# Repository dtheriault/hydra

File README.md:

The Hydra Project
======================================================================================

The Hydra project is a collaborative effort between N1GP and NO1D in an attempt
to produce a 'n' port CW/RTTY Skimmer platform based on RTL SDR technology.

The work is heavily leveraged from existing projects such as cuSDR and rtl-sdr 
development efforts.  

Changes and focus has been optimizing and supporting small embedded platforms such
as the Odroid C1/U3/XU3, Nvidia TK1 and RaspberryPI which may or may not be viable
platforms to execute on. 

The git repo allows us to share code changes easily using GIT and utilize GitHub to 
track issues and changes.  In the end, Rick will push changes made here up stream
to main projects librtlhpsdr and cusdr should they be deemed suitible for mainstream
users.

Challenges:
======================================================================================

    -- Optimizing code bases to run fast/efficiently on ARM based platforms
    -- Providing reliable support for up to 8 RTL dongles
    -- Create tools useful for calibration of RTL dongles for accurate CW Skimmer spot
       reporting in the Reverse Beacon Network (RBN).
    -- Develop unique hardware which includes front end filters, attenuator, mixer, 
       multiport coupler, amplifiers to ease integration with low cost RTLSDR dongles.
    -- Unique hardware packaging 

Project Organization:
======================================================================================
    -- Hydra             Top Level

      -- Software         Software Top Level
          -- librtlsdr    RTL Libraries and tools
          -- cusdrk       cuSDR GUI Application
          -- plotter      Skimmer Plotter, QRZ/RBN tools

      -- Hardware         Hardware Top Level
          -- Schematic    Schematic data in Eagle format
          -- Boards       ditto
          -- BOM          BOM files
          -- Mechanicals  Hardware Case information

      -- Documentation
          -- Specifications	
          -- Test Plans		
          -- Measurement Data

      -- Testing
          -- Scripts and Test Plans

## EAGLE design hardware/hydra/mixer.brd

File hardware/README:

This is the HW tree, schematics, pcb layouts, BOM's etc.

-----------------------------------------------------------------------------
Change Log:

25.Jun.2015  Initial submit of hardware files for Eagle development

-----------------------------------------------------------------------------
Directories: 

medusa/hardware

        top level hardware tree

hydra/

        Eagle schematic and board files for Receiver and Mixer boards
        Includes first pass BOM
        Includes .pdf's of board layouts suitable for printing

libraries/

          Eagle custom parts library files.  Add to Eagle ${EAGLE_LIBRARIES} 
          directory.

multicoupler/

          Early 8 port 75 ohm multi-coupler using Minicircuits component

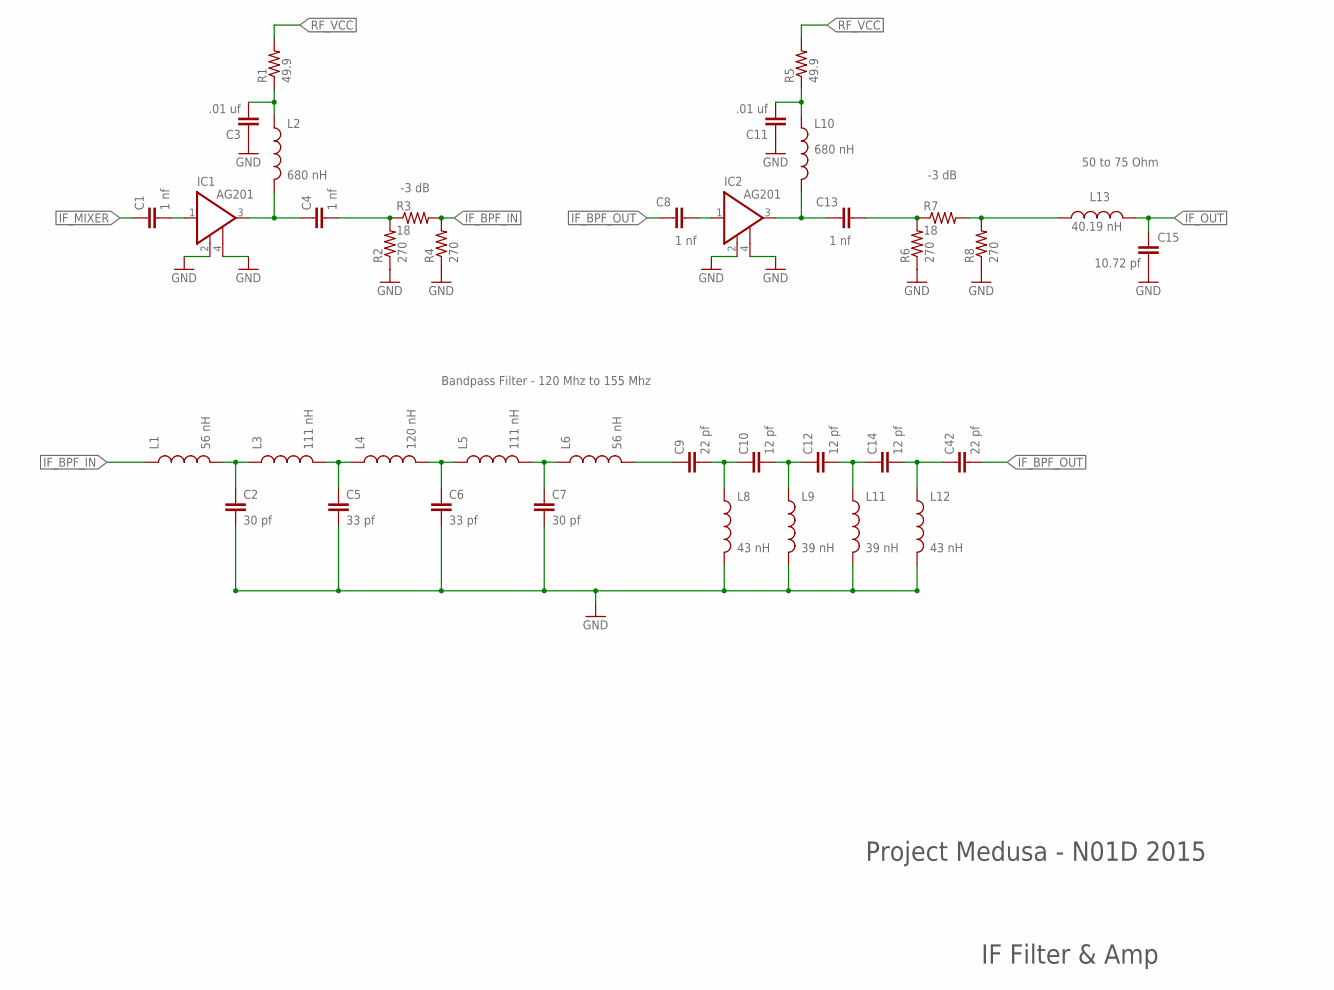
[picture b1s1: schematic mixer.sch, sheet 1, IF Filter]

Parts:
C1, C4, C8, C13: 1 nf; 0805
C2, C7: 30 pf; 0805
C3, C11: .01 uf; 0805
C5, C6: 33 pf; 0805
C9, C42: 22 pf; 0805
C10, C12, C14: 12 pf; 0805
C15: 10.72 pf; 0805
IC1, IC2: AG201; WW
L1, L6: 56 nH; 318-2
L2, L10: 680 nH; 0805
L3, L5: 111 nH; 319-2
L4: 120 nH; 318-2
L8, L12: 43 nH; 457-43
L9, L11: 39 nH; 457-39
L13: 40.19 nH; C0402
R1, R5: 49.9; 0805
R2, R4, R6, R8: 270; 1206
R3, R7: 18; 1206

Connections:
GND: C2.2, C3.1, C5.2, C6.2, C7.2, C11.1, C15.1, IC1.2 (GND), IC1.4 (GND), IC2.2 (GND), IC2.4 (GND), L8.P$2 (2), L9.P$2 (2), L11.P$2 (2), L12.P$2 (2), R2.1, R4.1, R6.1, R8.1; also elsewhere on the board
IF_BPF_IN: L1.P$1 (1), R3.2, R4.2
IF_BPF_OUT: C8.1, C42.2
IF_MIXER: C1.1; also elsewhere on the board
IF_OUT: C15.2, L13.2; also elsewhere on the board
unnamed: C2.1, L1.P$2 (2), L3.P$1 (1)
unnamed: C5.1, L3.P$2 (2), L4.P$1 (1)
unnamed: C6.1, L4.P$2 (2), L5.P$1 (1)
unnamed: C7.1, L5.P$2 (2), L6.P$1 (1)
unnamed: C9.1, L6.P$2 (2)
unnamed: C9.2, C10.1, L8.P$1 (1)
unnamed: C10.2, C12.1, L9.P$1 (1)
unnamed: C12.2, C14.1, L11.P$1 (1)
unnamed: C1.2, IC1.1 (RFIN)
unnamed: C4.1, IC1.3 (RFOUT/DCIN), L2.2
unnamed: C3.2, L2.1, R1.1
unnamed: C4.2, R2.2, R3.1
unnamed: C8.2, IC2.1 (RFIN)
unnamed: C13.1, IC2.3 (RFOUT/DCIN), L10.2
unnamed: C11.2, L10.1, R5.1
unnamed: C13.2, R6.2, R7.1
unnamed: L13.1, R7.2, R8.2
unnamed: C14.2, C42.1, L12.P$1 (1)
RF_VCC: R1.2, R5.2; also elsewhere on the board

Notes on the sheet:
Bandpass Filter - 120 Mhz to 155 Mhz
50 to 75 Ohm
-3 dB
Project Medusa - N01D 2015
IF Filter & Amp

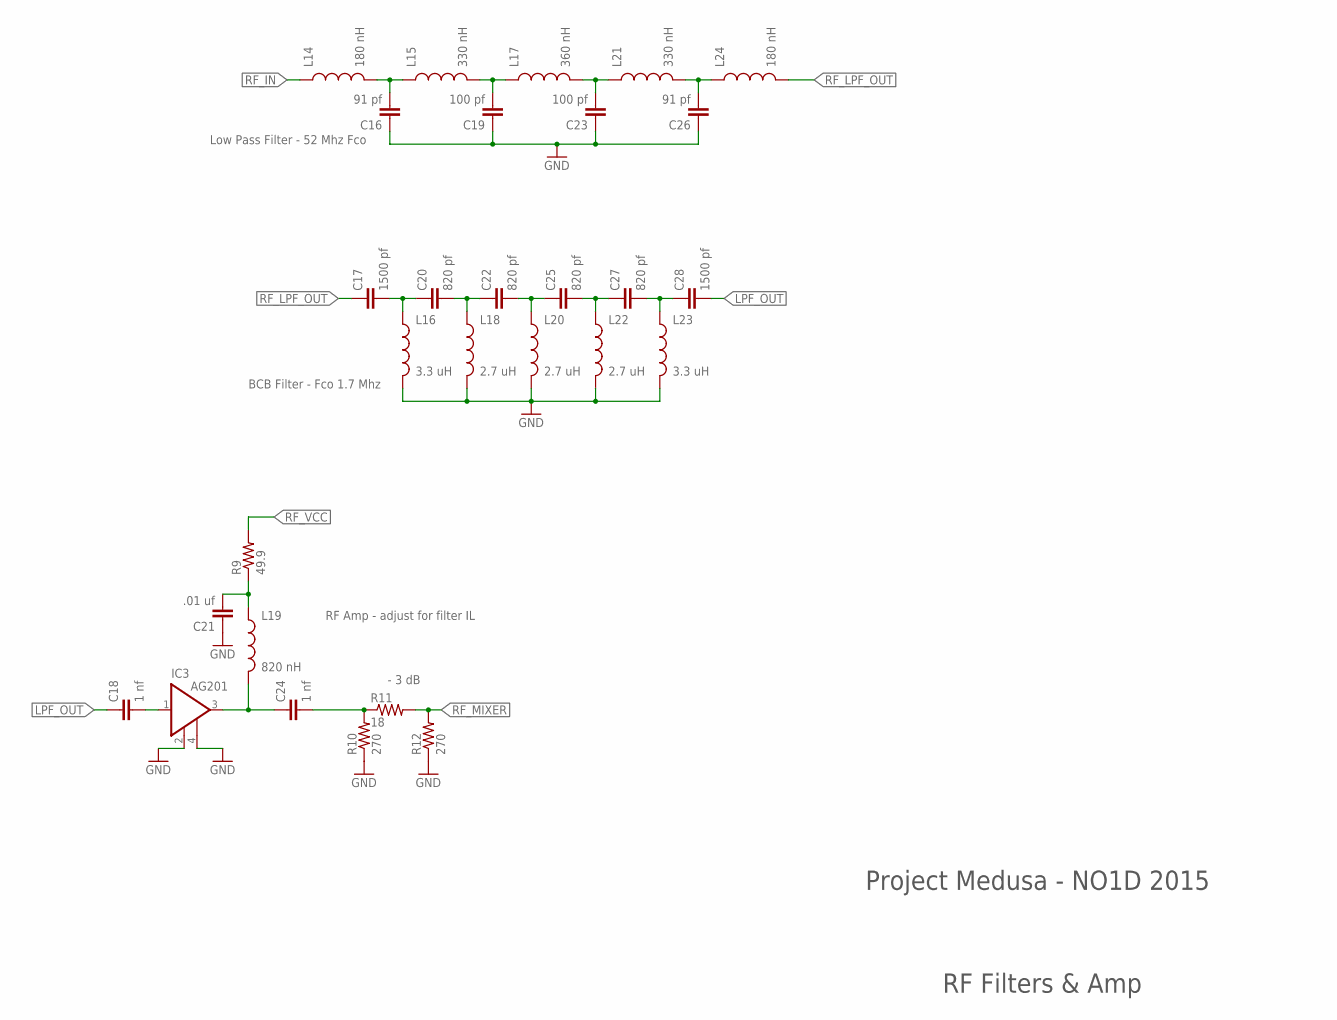
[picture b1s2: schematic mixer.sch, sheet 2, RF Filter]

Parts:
C16, C26: 91 pf; 0805
C17, C28: 1500 pf; 0805
C18, C24: 1 nf; 0805
C19, C23: 100 pf; 0805
C20, C22, C25, C27: 820 pf; 0805
C21: .01 uf; 0805
IC3: AG201; WW
L14, L24: 180 nH; 438-2-180
L15, L21: 330 nH; 438-2-330
L16, L23: 3.3 uH; RLB0912
L17: 360 nH; 438-2-360
L18, L20, L22: 2.7 uH; RLB0912
L19: 820 nH; 0805
R9: 49.9; 0805
R10, R12: 270; 1206
R11: 18; 1206

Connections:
GND: C16.1, C19.1, C21.1, C23.1, C26.1, IC3.2 (GND), IC3.4 (GND), L16.2, L18.2, L20.2, L22.2, L23.2, R10.1, R12.1; also elsewhere on the board
LPF_OUT: C18.1, C28.2
unnamed: C18.2, IC3.1 (RFIN)
unnamed: C24.1, IC3.3 (RFOUT/DCIN), L19.2
unnamed: C21.2, L19.1, R9.1
unnamed: C24.2, R10.2, R11.1
unnamed: C16.2, L14.P$2 (2), L15.P$1 (1)
unnamed: C19.2, L15.P$2 (2), L17.P$1 (1)
unnamed: C23.2, L17.P$2 (2), L21.P$1 (1)
unnamed: C26.2, L21.P$2 (2), L24.P$1 (1)
unnamed: C17.2, C20.1, L16.1
unnamed: C20.2, C22.1, L18.1
unnamed: C22.2, C25.1, L20.1
unnamed: C25.2, C27.1, L22.1
unnamed: C27.2, C28.1, L23.1
RF_IN: L14.P$1 (1); also elsewhere on the board
RF_LPF_OUT: C17.1, L24.P$2 (2)
RF_MIXER: R11.2, R12.2; also elsewhere on the board
RF_VCC: R9.2; also elsewhere on the board

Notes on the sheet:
Low Pass Filter - 52 Mhz Fco
BCB Filter - Fco 1.7 Mhz
- 3 dB
RF Amp - adjust for filter IL
Project Medusa - NO1D 2015
RF Filters & Amp

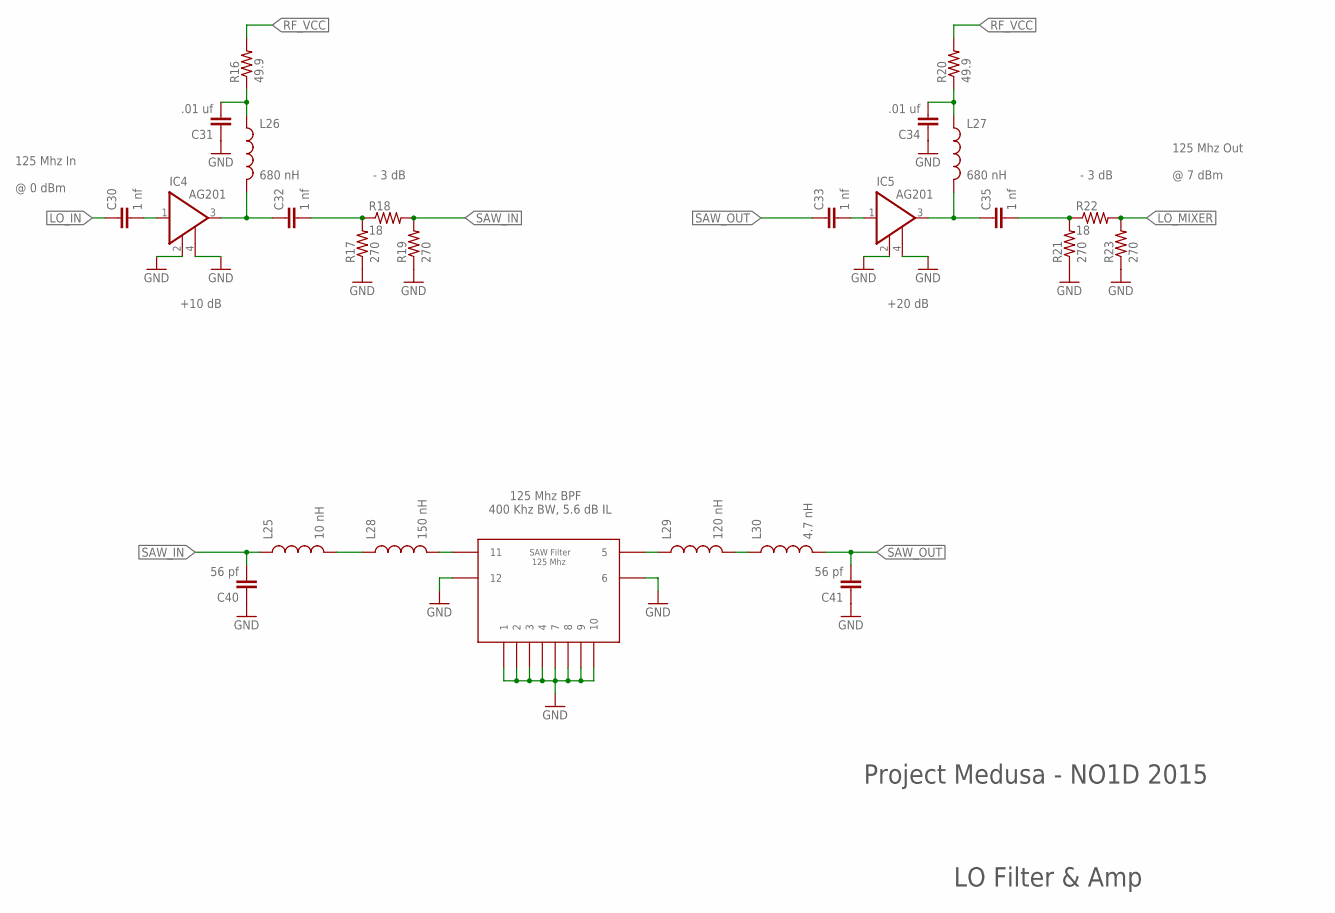
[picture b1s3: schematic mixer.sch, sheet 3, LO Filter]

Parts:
C30, C32, C33, C35: 1 nf; 0805
C31, C34: .01 uf; 0805
C40, C41: 56 pf; 0805
IC4, IC5: AG201; WW
L25: 10 nH; C0402
L26, L27: 680 nH; 0805
L28: 150 nH; 0805
L29: 120 nH; 0805
L30: 4.7 nH; C0402
R16, R20: 49.9; 0805
R17, R19, R21, R23: 270; 1206
R18, R22: 18; 1206
SAW1: SAW-125MHZ; SAW-125M-SMP

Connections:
GND: C31.1, C34.1, C40.1, C41.1, IC4.2 (GND), IC4.4 (GND), IC5.2 (GND), IC5.4 (GND), R17.1, R19.1, R21.1, R23.1, SAW1.P$1 (1), SAW1.P$2 (2), SAW1.P$3 (3), SAW1.P$4 (4), SAW1.P$6 (6), SAW1.P$7 (7), SAW1.P$8 (8), SAW1.P$9 (9), SAW1.P$10 (10), SAW1.P$12 (12); also elsewhere on the board
LO_IN: C30.1; also elsewhere on the board
LO_MIXER: R22.2, R23.2; also elsewhere on the board
unnamed: C30.2, IC4.1 (RFIN)
unnamed: C32.1, IC4.3 (RFOUT/DCIN), L26.2
unnamed: C31.2, L26.1, R16.1
unnamed: C32.2, R17.2, R18.1
unnamed: C33.2, IC5.1 (RFIN)
unnamed: C35.1, IC5.3 (RFOUT/DCIN), L27.2
unnamed: C34.2, L27.1, R20.1
unnamed: C35.2, R21.2, R22.1
unnamed: L25.2, L28.1
unnamed: L29.2, L30.1
unnamed: L28.2, SAW1.P$11 (11)
unnamed: L29.1, SAW1.P$5 (5)
RF_VCC: R16.2, R20.2; also elsewhere on the board
SAW_IN: C40.2, L25.1, R18.2, R19.2
SAW_OUT: C33.1, C41.2, L30.2

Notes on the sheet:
125 Mhz In @ 0 dBm
125 Mhz Out @ 7 dBm
+10 dB
+20 dB
- 3 dB
125 Mhz BPF 400 Khz BW, 5.6 dB IL
Project Medusa - NO1D 2015
LO Filter & Amp

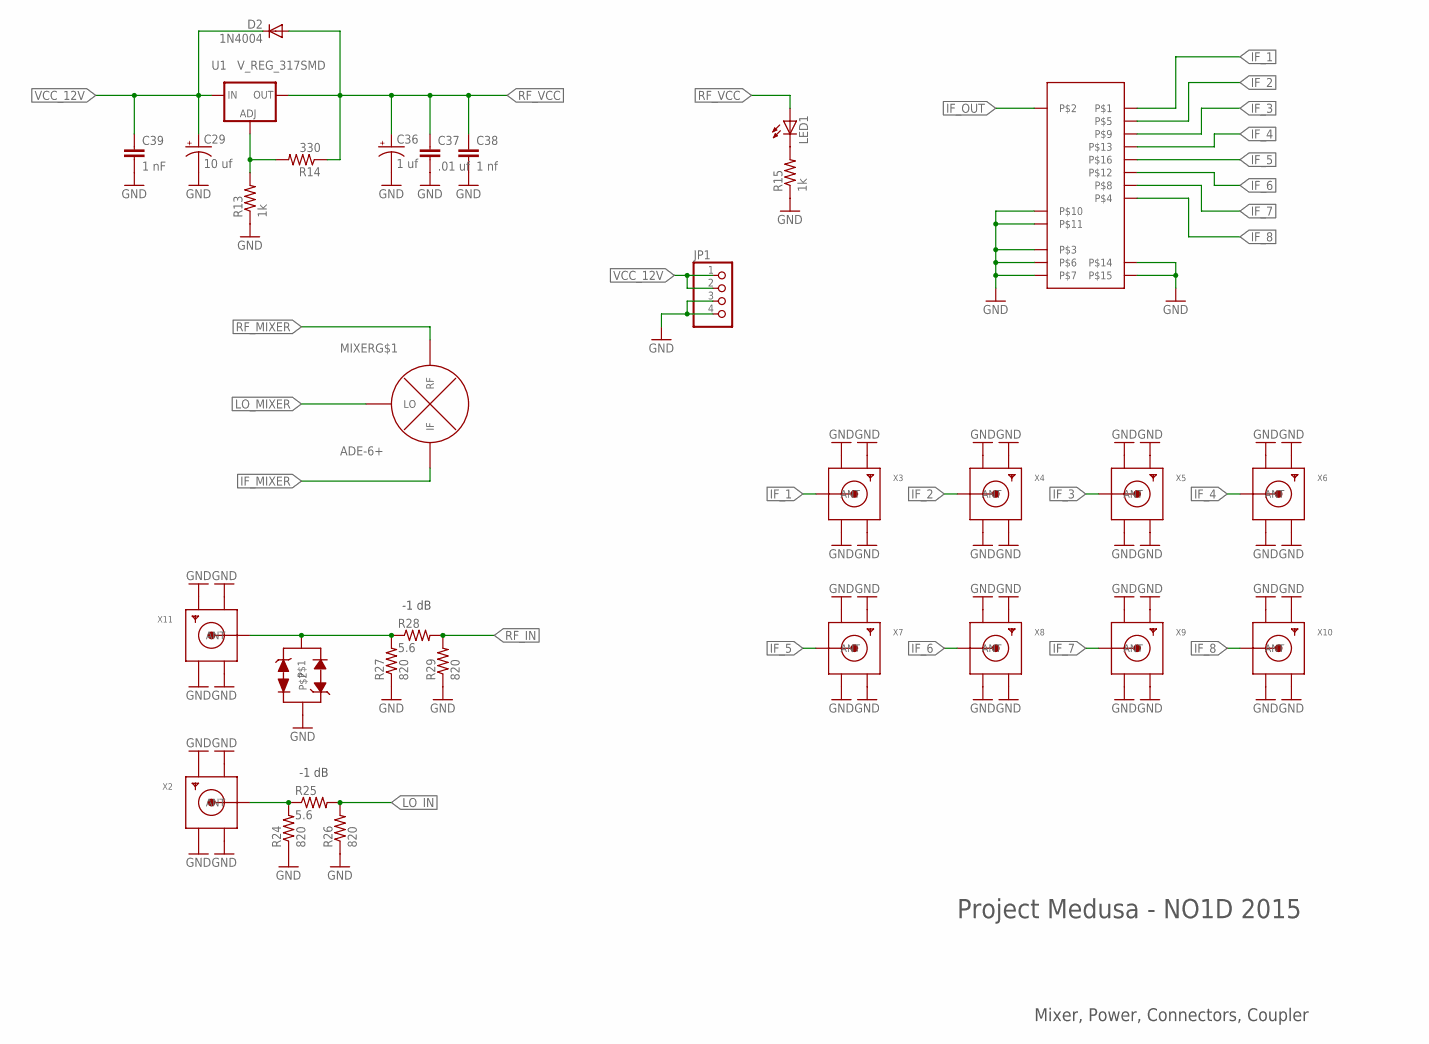
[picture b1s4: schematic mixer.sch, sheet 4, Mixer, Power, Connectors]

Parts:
C29: 10 uf; EIA3216
C36: 1 uf; EIA3216
C37: .01 uf; 0805
C38: 1 nf; 0805
C39: 1 nF; 0805
D2: 1N4004; DO41-10
JP1: PINHD-1X4; 1X04
LED1: LEDSML0805; SML0805
MIXER: ADE-6+; ADE6
R13, R15: 1k; 1206
R14: 330; 1206
R24, R26, R27, R29: 820; 1206
R25, R28: 5.6; 1206
U1: V_REG_317SMD; SOT223
U$1: PSC-8-1-75THROUGH_HOLE; PSC-8-1-75
U$9: TVS-DIODE; SOD323
X2, X3, X4, X5, X6, X7, X8, X9, X10, X11: SMACONNECTOR_EDGE; SMA_EDGELAUNCH

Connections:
GND: C29.C (-), C36.C (-), C37.2, C38.2, C39.2, JP1.3, JP1.4, MIXER.P$1 (GND), MIXER.P$4 (GND), MIXER.P$5 (GND), R13.1, R15.1, R24.1, R26.1, R27.1, R29.1, U$1.P$3, U$1.P$6, U$1.P$7, U$1.P$10, U$1.P$11, U$1.P$14, U$1.P$15, U$9.P$3, X2.GND@1 (GND4), X2.GND@2 (GND3), X2.GND@3 (GND2), X2.GND@4 (GND1), X3.GND@1 (GND4), X3.GND@2 (GND3), X3.GND@3 (GND2), X3.GND@4 (GND1), X4.GND@1 (GND4), X4.GND@2 (GND3), X4.GND@3 (GND2), X4.GND@4 (GND1), X5.GND@1 (GND4), X5.GND@2 (GND3), X5.GND@3 (GND2), X5.GND@4 (GND1), X6.GND@1 (GND4), X6.GND@2 (GND3), X6.GND@3 (GND2), X6.GND@4 (GND1), X7.GND@1 (GND4), X7.GND@2 (GND3), X7.GND@3 (GND2), X7.GND@4 (GND1), X8.GND@1 (GND4), X8.GND@2 (GND3), X8.GND@3 (GND2), X8.GND@4 (GND1), X9.GND@1 (GND4), X9.GND@2 (GND3), X9.GND@3 (GND2), X9.GND@4 (GND1), X10.GND@1 (GND4), X10.GND@2 (GND3), X10.GND@3 (GND2), X10.GND@4 (GND1), X11.GND@1 (GND4), X11.GND@2 (GND3), X11.GND@3 (GND2), X11.GND@4 (GND1); also elsewhere on the board
IF_1: U$1.P$1, X3.P (ANT)
IF_2: U$1.P$5, X4.P (ANT)
IF_3: U$1.P$9, X5.P (ANT)
IF_4: U$1.P$13, X6.P (ANT)
IF_5: U$1.P$16, X7.P (ANT)
IF_6: U$1.P$12, X8.P (ANT)
IF_7: U$1.P$8, X9.P (ANT)
IF_8: U$1.P$4, X10.P (ANT)
IF_MIXER: MIXER.P$2 (IF); also elsewhere on the board
IF_OUT: U$1.P$2; also elsewhere on the board
LO_IN: R25.2, R26.2; also elsewhere on the board
LO_MIXER: MIXER.P$6 (LO); also elsewhere on the board
unnamed: R13.2, R14.2, U1.1 (ADJ)
unnamed: R24.2, R25.1, X2.P (ANT)
unnamed: R27.2, R28.1, U$9.P$1, X11.P (ANT)
unnamed: LED1.C, R15.2
RF_IN: R28.2, R29.2; also elsewhere on the board
RF_MIXER: MIXER.P$3 (RF); also elsewhere on the board
RF_VCC: C36.A (+), C37.1, C38.1, D2.A, LED1.A, R14.1, U1.2 (OUT); also elsewhere on the board
VCC_12V: C29.A (+), C39.1, D2.C, JP1.1, JP1.2, U1.3 (IN)

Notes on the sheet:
-1 dB
Project Medusa - NO1D 2015
Mixer, Power, Connectors, Coupler

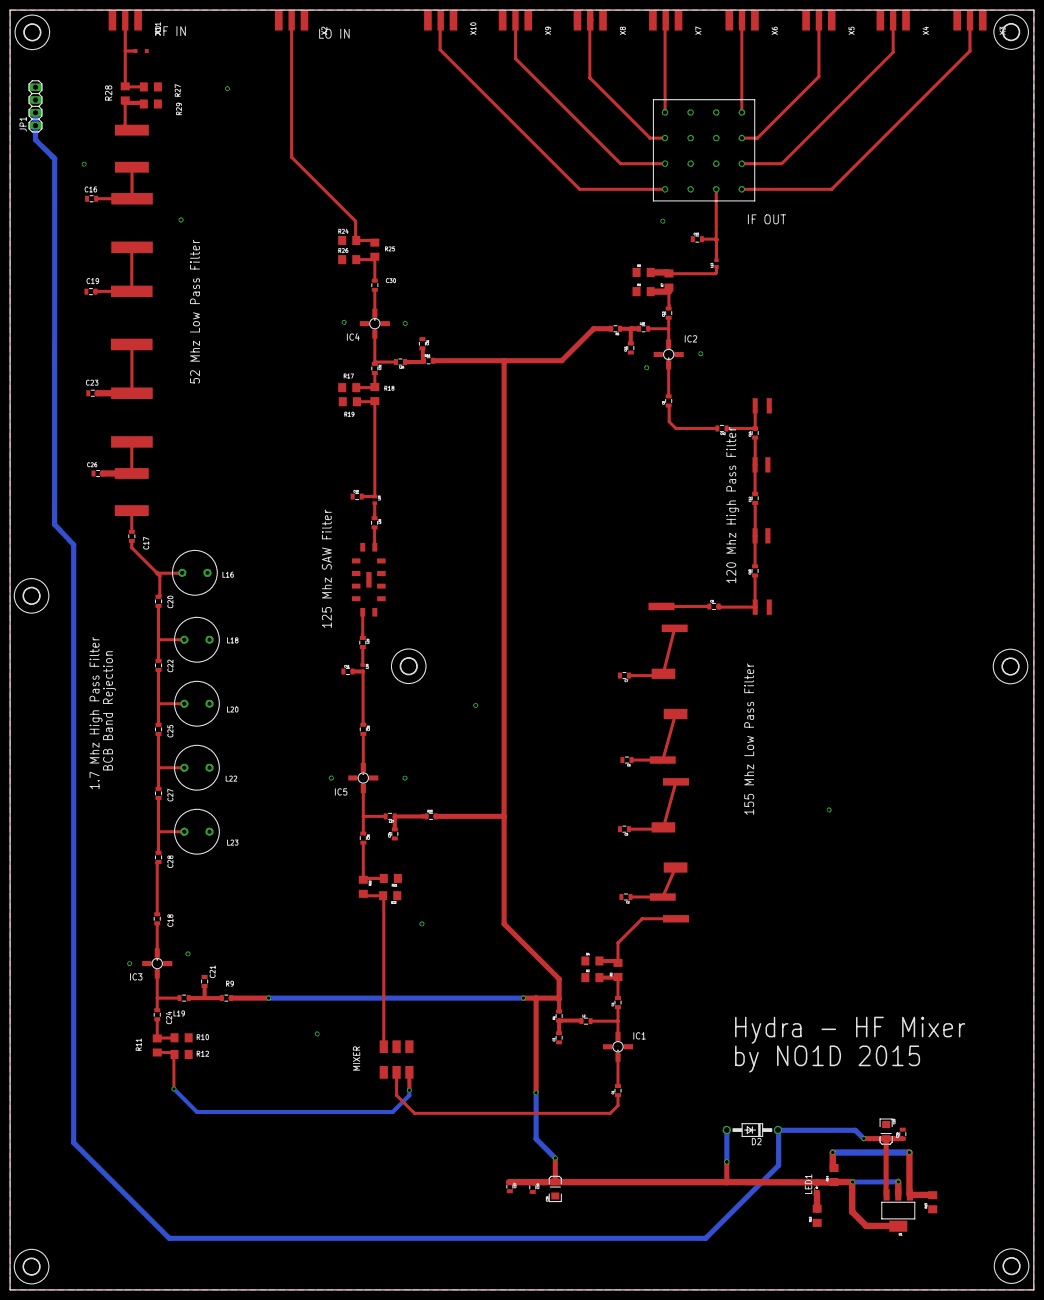
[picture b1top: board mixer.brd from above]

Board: 2 copper layers, 203.2 x 254.0 mm, 130 parts (0 on the bottom side), 70 nets.

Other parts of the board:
U$2, U$3, U$4, U$5, U$6, U$7, U$8: 3,2

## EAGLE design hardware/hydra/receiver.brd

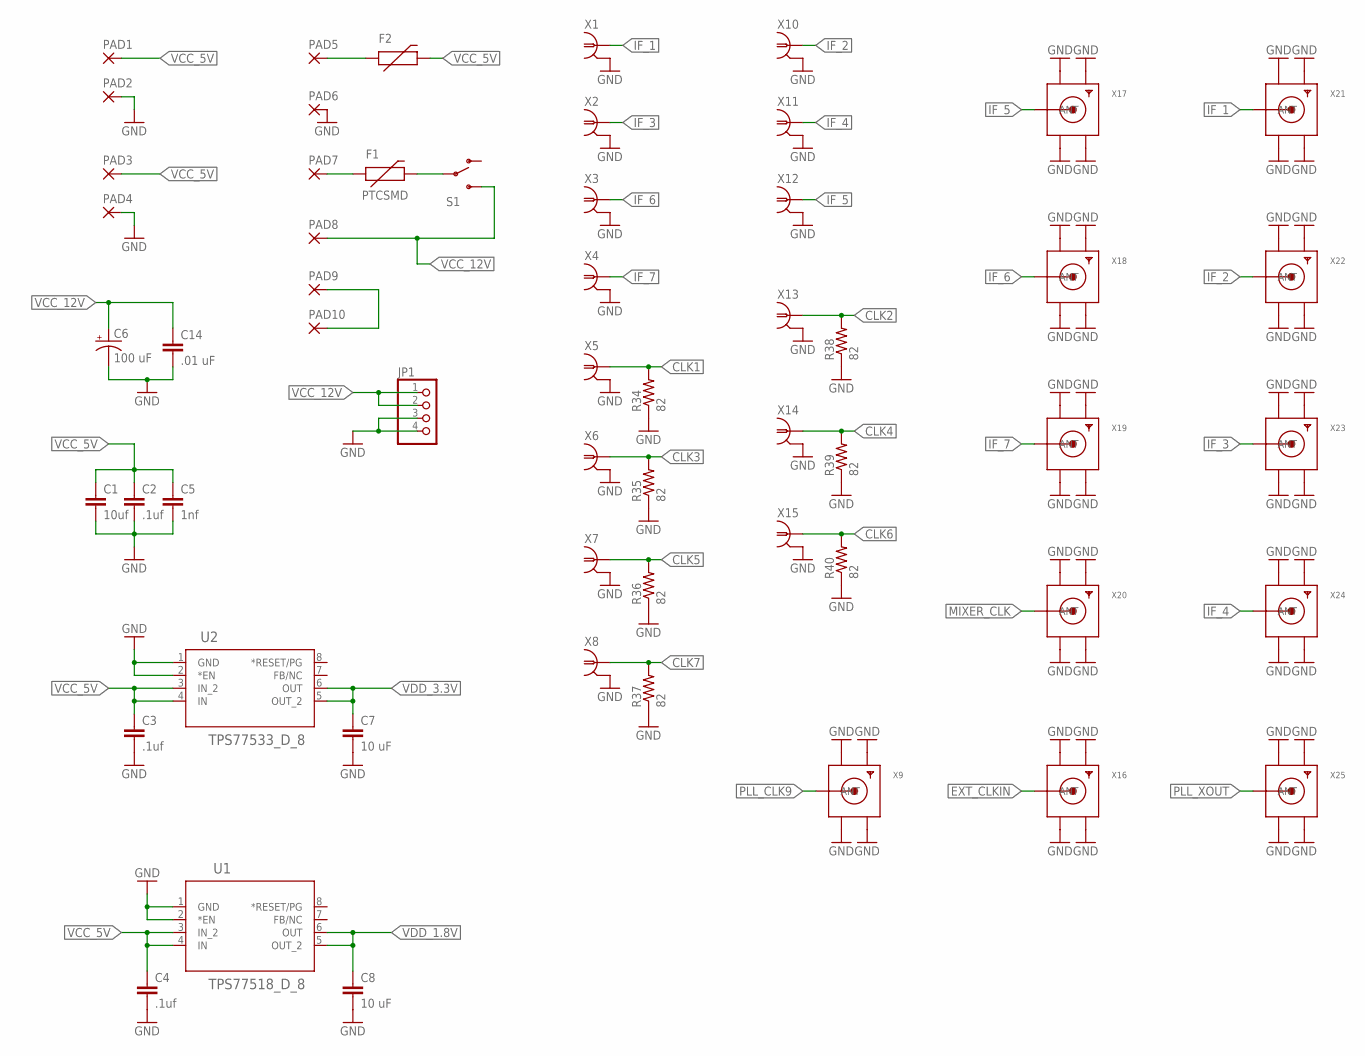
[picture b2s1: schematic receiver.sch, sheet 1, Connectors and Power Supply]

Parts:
C1: 10uf; 1206
C2, C3, C4: .1uf; 0805
C5: 1nf; 0805
C6: 100 uF; CPOL-RADIAL-1000UF-25V
C7, C8: 10 uF; 1206
C14: .01 uF; 0805
F1, F2: PTCSMD; PTC-1206
JP1: PINHD-1X4; 1X04
PAD1, PAD2, PAD3, PAD4, PAD5, PAD6, PAD7, PAD8, PAD9, PAD10: WIREPAD2,54/0,9; 2,54/0,9
R34, R35, R36, R37, R38, R39, R40: 82; 0805
S1: SWITCH-SPDTPTH; SWITCH-SPDT
U1: TPS77518_D_8; D8
U2: TPS77533_D_8; D8
X1, X2, X3, X4, X5, X6, X7, X8, X10, X11, X12, X13, X14, X15: LTI-SASF54GT
X9, X16, X17, X18, X19, X20, X21, X22, X23, X24, X25: SMACONNECTOR_EDGE; SMA_EDGELAUNCH

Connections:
CLK1: R34.2, X5.1; also elsewhere on the board
CLK2: R38.2, X13.1; also elsewhere on the board
CLK3: R35.2, X6.1; also elsewhere on the board
CLK4: R39.2, X14.1; also elsewhere on the board
CLK5: R36.2, X7.1; also elsewhere on the board
CLK6: R40.2, X15.1; also elsewhere on the board
CLK7: R37.2, X8.1; also elsewhere on the board
EXT_CLKIN: X16.P (ANT); also elsewhere on the board
GND: C1.2, C2.2, C3.2, C4.2, C5.2, C6.-, C7.2, C8.2, C14.2, JP1.3, JP1.4, PAD2.1, PAD4.1, PAD6.1, R34.1, R35.1, R36.1, R37.1, R38.1, R39.1, R40.1, U1.1 (GND), U1.2 (*EN), U2.1 (GND), U2.2 (*EN), X1.2, X1.3 (2), X1.4 (2), X1.5 (2), X2.2, X2.3 (2), X2.4 (2), X2.5 (2), X3.2, X3.3 (2), X3.4 (2), X3.5 (2), X4.2, X4.3 (2), X4.4 (2), X4.5 (2), X5.2, X5.3 (2), X5.4 (2), X5.5 (2), X6.2, X6.3 (2), X6.4 (2), X6.5 (2), X7.2, X7.3 (2), X7.4 (2), X7.5 (2), X8.2, X8.3 (2), X8.4 (2), X8.5 (2), X9.GND@1 (GND4), X9.GND@2 (GND3), X9.GND@3 (GND2), X9.GND@4 (GND1), X10.2, X10.3 (2), X10.4 (2), X10.5 (2), X11.2, X11.3 (2), X11.4 (2), X11.5 (2), X12.2, X12.3 (2), X12.4 (2), X12.5 (2), X13.2, X13.3 (2), X13.4 (2), X13.5 (2), X14.2, X14.3 (2), X14.4 (2), X14.5 (2), X15.2, X15.3 (2), X15.4 (2), X15.5 (2), X16.GND@1 (GND4), X16.GND@2 (GND3), X16.GND@3 (GND2), X16.GND@4 (GND1), X17.GND@1 (GND4), X17.GND@2 (GND3), X17.GND@3 (GND2), X17.GND@4 (GND1), X18.GND@1 (GND4), X18.GND@2 (GND3), X18.GND@3 (GND2), X18.GND@4 (GND1), X19.GND@1 (GND4), X19.GND@2 (GND3), X19.GND@3 (GND2), X19.GND@4 (GND1), X20.GND@1 (GND4), X20.GND@2 (GND3), X20.GND@3 (GND2), X20.GND@4 (GND1), X21.GND@1 (GND4), X21.GND@2 (GND3), X21.GND@3 (GND2), X21.GND@4 (GND1), X22.GND@1 (GND4), X22.GND@2 (GND3), X22.GND@3 (GND2), X22.GND@4 (GND1), X23.GND@1 (GND4), X23.GND@2 (GND3), X23.GND@3 (GND2), X23.GND@4 (GND1), X24.GND@1 (GND4), X24.GND@2 (GND3), X24.GND@3 (GND2), X24.GND@4 (GND1), X25.GND@1 (GND4), X25.GND@2 (GND3), X25.GND@3 (GND2), X25.GND@4 (GND1); also elsewhere on the board
IF_1: X1.1, X21.P (ANT)
IF_2: X10.1, X22.P (ANT)
IF_3: X2.1, X23.P (ANT)
IF_4: X11.1, X24.P (ANT)
IF_5: X12.1, X17.P (ANT)
IF_6: X3.1, X18.P (ANT)
IF_7: X4.1, X19.P (ANT)
MIXER_CLK: X20.P (ANT); also elsewhere on the board
unnamed: F1.1, PAD7.1
unnamed: F1.2, S1.2
unnamed: F2.1, PAD5.1
unnamed: PAD9.1, PAD10.1
PLL_CLK9: X9.P (ANT); also elsewhere on the board
PLL_XOUT: X25.P (ANT); also elsewhere on the board
VCC_5V: C1.1, C2.1, C3.1, C4.1, C5.1, F2.2, PAD1.1, PAD3.1, U1.3 (IN_2), U1.4 (IN), U2.3 (IN_2), U2.4 (IN); also elsewhere on the board
VCC_12V: C6.+, C14.1, JP1.1, JP1.2, PAD8.1, S1.3 (S)
VDD_1.8V: C8.1, U1.5 (OUT_2), U1.6 (OUT); also elsewhere on the board
VDD_3.3V: C7.1, U2.5 (OUT_2), U2.6 (OUT); also elsewhere on the board

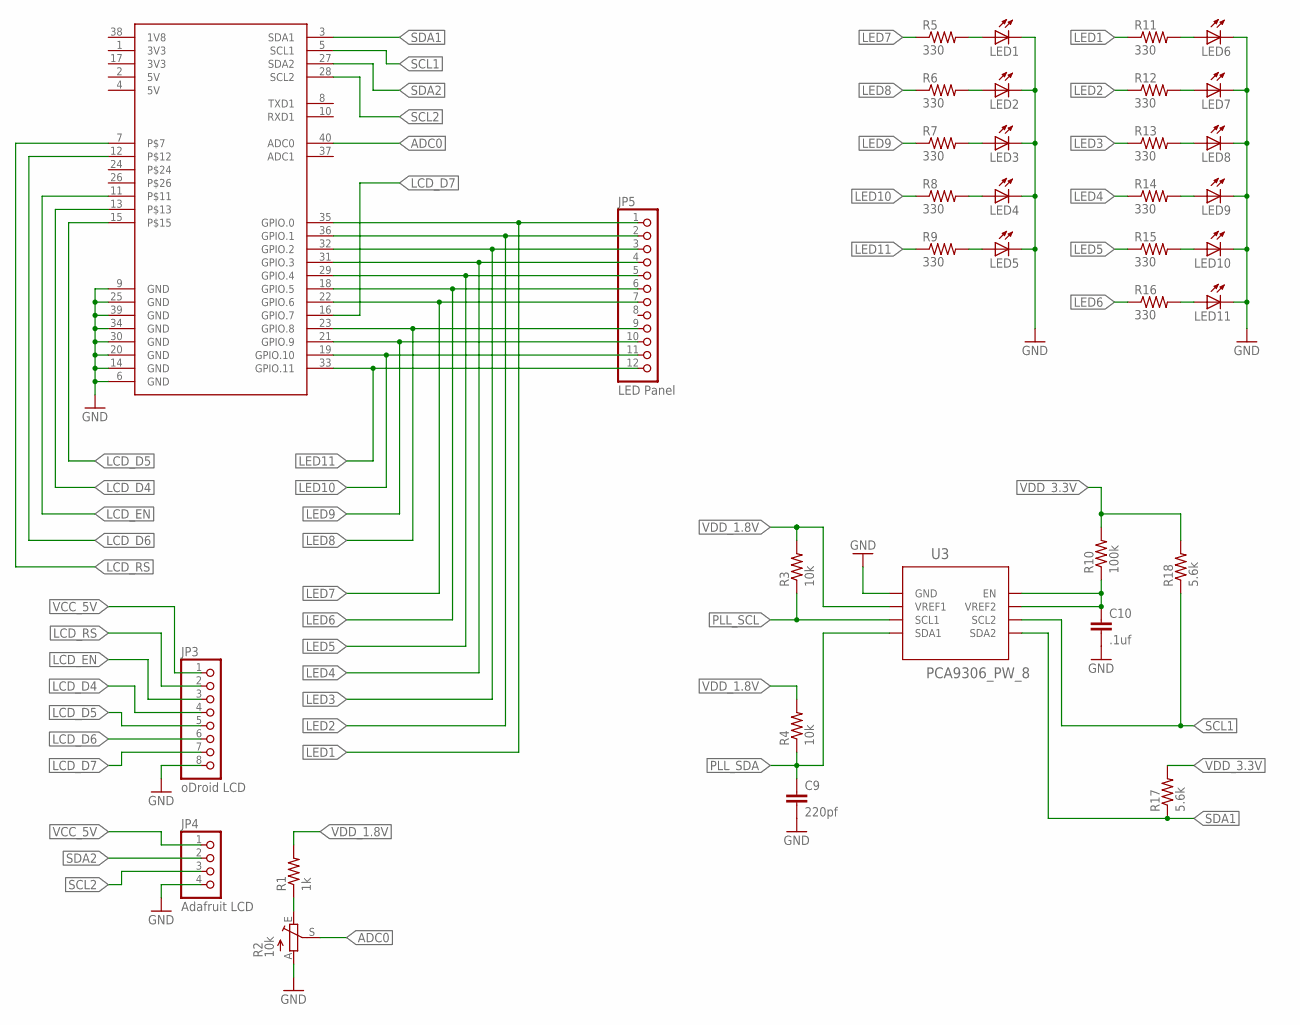
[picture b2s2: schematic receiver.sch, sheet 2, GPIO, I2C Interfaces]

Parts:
C9: 220pf; 0805
C10: .1uf; 0805
JP2: C1_GPIO; 2X20-BIG
JP3: oDroid LCD; 1X08
JP4: Adafruit LCD; 1X04
JP5: LED Panel; 1X12
LED1, LED2, LED3, LED4, LED5, LED6, LED7, LED8, LED9, LED10, LED11: LEDCHIPLED_1206; CHIPLED_1206
R1: 1k; 0805
R2: 10k; B64Y
R3, R4: 10k; 0805
R5, R6, R7, R8, R9, R11, R12, R13, R14, R15, R16: 330; 0805
R10: 100k; 0805
R17, R18: 5.6k; 0805
U3: PCA9306_PW_8; PW8

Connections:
ADC0: JP2.40 (ADC0), R2.S
GND: C9.2, C10.2, JP2.6 (GND), JP2.9 (GND), JP2.14 (GND), JP2.20 (GND), JP2.25 (GND), JP2.30 (GND), JP2.34 (GND), JP2.39 (GND), JP3.8, JP4.4, LED1.C, LED2.C, LED3.C, LED4.C, LED5.C, LED6.C, LED7.C, LED8.C, LED9.C, LED10.C, LED11.C, R2.A, U3.1 (GND); also elsewhere on the board
LCD_D4: JP2.13, JP3.4
LCD_D5: JP2.15, JP3.5
LCD_D6: JP2.12, JP3.6
LCD_D7: JP2.16 (GPIO.7), JP3.7
LCD_EN: JP2.11, JP3.3
LCD_RS: JP2.7, JP3.2
LED1: JP2.35 (GPIO.0), JP5.1, R11.1
LED2: JP2.36 (GPIO.1), JP5.2, R12.1
LED3: JP2.32 (GPIO.2), JP5.3, R13.1
LED4: JP2.31 (GPIO.3), JP5.4, R14.1
LED5: JP2.29 (GPIO.4), JP5.5, R15.1
LED6: JP2.18 (GPIO.5), JP5.6, R16.1
LED7: JP2.22 (GPIO.6), JP5.7, R5.1
LED8: JP2.23 (GPIO.8), JP5.9, R6.1
LED9: JP2.21 (GPIO.9), JP5.10, R7.1
LED10: JP2.19 (GPIO.10), JP5.11, R8.1
LED11: JP2.33 (GPIO.11), JP5.12, R9.1
unnamed: C10.1, R10.1, U3.7 (VREF2), U3.8 (EN)
unnamed: R1.1, R2.E
unnamed: LED5.A, R9.2
unnamed: LED4.A, R8.2
unnamed: LED3.A, R7.2
unnamed: LED2.A, R6.2
unnamed: LED1.A, R5.2
unnamed: LED11.A, R16.2
unnamed: LED10.A, R15.2
unnamed: LED9.A, R14.2
unnamed: LED8.A, R13.2
unnamed: LED7.A, R12.2
unnamed: LED6.A, R11.2
PLL_SCL: R3.1, U3.3 (SCL1); also elsewhere on the board
PLL_SDA: C9.1, R4.1, U3.4 (SDA1); also elsewhere on the board
SCL1: JP2.5 (SCL1), R18.1, U3.6 (SCL2)
SCL2: JP2.28 (SCL2), JP4.3
SDA1: JP2.3 (SDA1), R17.1, U3.5 (SDA2)
SDA2: JP2.27 (SDA2), JP4.2
VCC_5V: JP3.1, JP4.1; also elsewhere on the board
VDD_1.8V: R1.2, R3.2, R4.2, U3.2 (VREF1); also elsewhere on the board
VDD_3.3V: R10.2, R17.2, R18.2; also elsewhere on the board

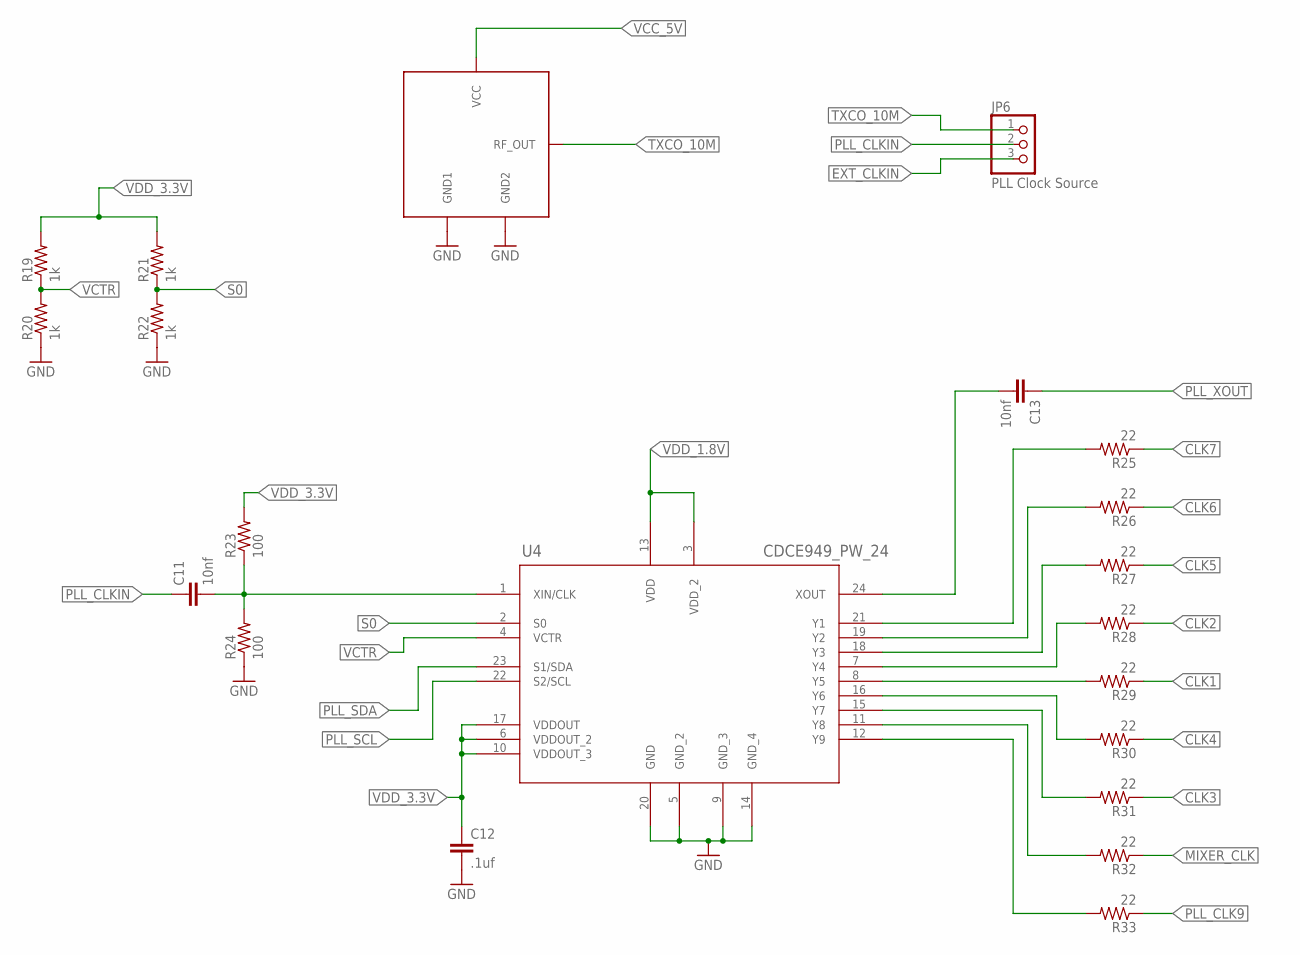
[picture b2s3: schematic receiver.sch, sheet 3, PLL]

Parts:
$3_194_$_2015-06-18_19-54-36: TXCO 10M; THRU-HOLE
C11, C13: 10nf; 0805
C12: .1uf; 0805
JP6: PLL Clock Source; 1X03
R19, R20, R21, R22: 1k; 0805
R23, R24: 100; 0805
R25, R26, R27, R28, R29, R30, R31, R32, R33: 22; 0805
U4: CDCE949_PW_24; PW24

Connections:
CLK1: R29.1; also elsewhere on the board
CLK2: R28.1; also elsewhere on the board
CLK3: R31.1; also elsewhere on the board
CLK4: R30.1; also elsewhere on the board
CLK5: R27.1; also elsewhere on the board
CLK6: R26.1; also elsewhere on the board
CLK7: R25.1; also elsewhere on the board
EXT_CLKIN: JP6.3; also elsewhere on the board
GND: $3_194_$_2015-06-18_19-54-36.GND1, $3_194_$_2015-06-18_19-54-36.GND2, C12.2, R20.1, R22.1, R24.1, U4.5 (GND_2), U4.9 (GND_3), U4.14 (GND_4), U4.20 (GND); also elsewhere on the board
MIXER_CLK: R32.1; also elsewhere on the board
unnamed: C11.2, R23.1, R24.2, U4.1 (XIN/CLK)
unnamed: C13.2, U4.24 (XOUT)
unnamed: R31.2, U4.15 (Y7)
unnamed: R25.2, U4.21 (Y1)
unnamed: R26.2, U4.19 (Y2)
unnamed: R27.2, U4.18 (Y3)
unnamed: R28.2, U4.7 (Y4)
unnamed: R29.2, U4.8 (Y5)
unnamed: R30.2, U4.16 (Y6)
unnamed: R32.2, U4.11 (Y8)
unnamed: R33.2, U4.12 (Y9)
PLL_CLK9: R33.1; also elsewhere on the board
PLL_CLKIN: C11.1, JP6.2
PLL_SCL: U4.22 (S2/SCL); also elsewhere on the board
PLL_SDA: U4.23 (S1/SDA); also elsewhere on the board
PLL_XOUT: C13.1; also elsewhere on the board
S0: R21.1, R22.2, U4.2 (S0)
TXCO_10M: $3_194_$_2015-06-18_19-54-36.RF_OUT, JP6.1
VCC_5V: $3_194_$_2015-06-18_19-54-36.VCC; also elsewhere on the board
VCTR: R19.1, R20.2, U4.4 (VCTR)
VDD_1.8V: U4.3 (VDD_2), U4.13 (VDD); also elsewhere on the board
VDD_3.3V: C12.1, R19.2, R21.2, R23.2, U4.6 (VDDOUT_2), U4.10 (VDDOUT_3), U4.17 (VDDOUT); also elsewhere on the board

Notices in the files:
parts and their libraries:
SparkFun-Capacitors: Licensing: Creative Commons ShareAlike 4.0 International - https://creativecommons.org/licenses/by-sa/4.0
